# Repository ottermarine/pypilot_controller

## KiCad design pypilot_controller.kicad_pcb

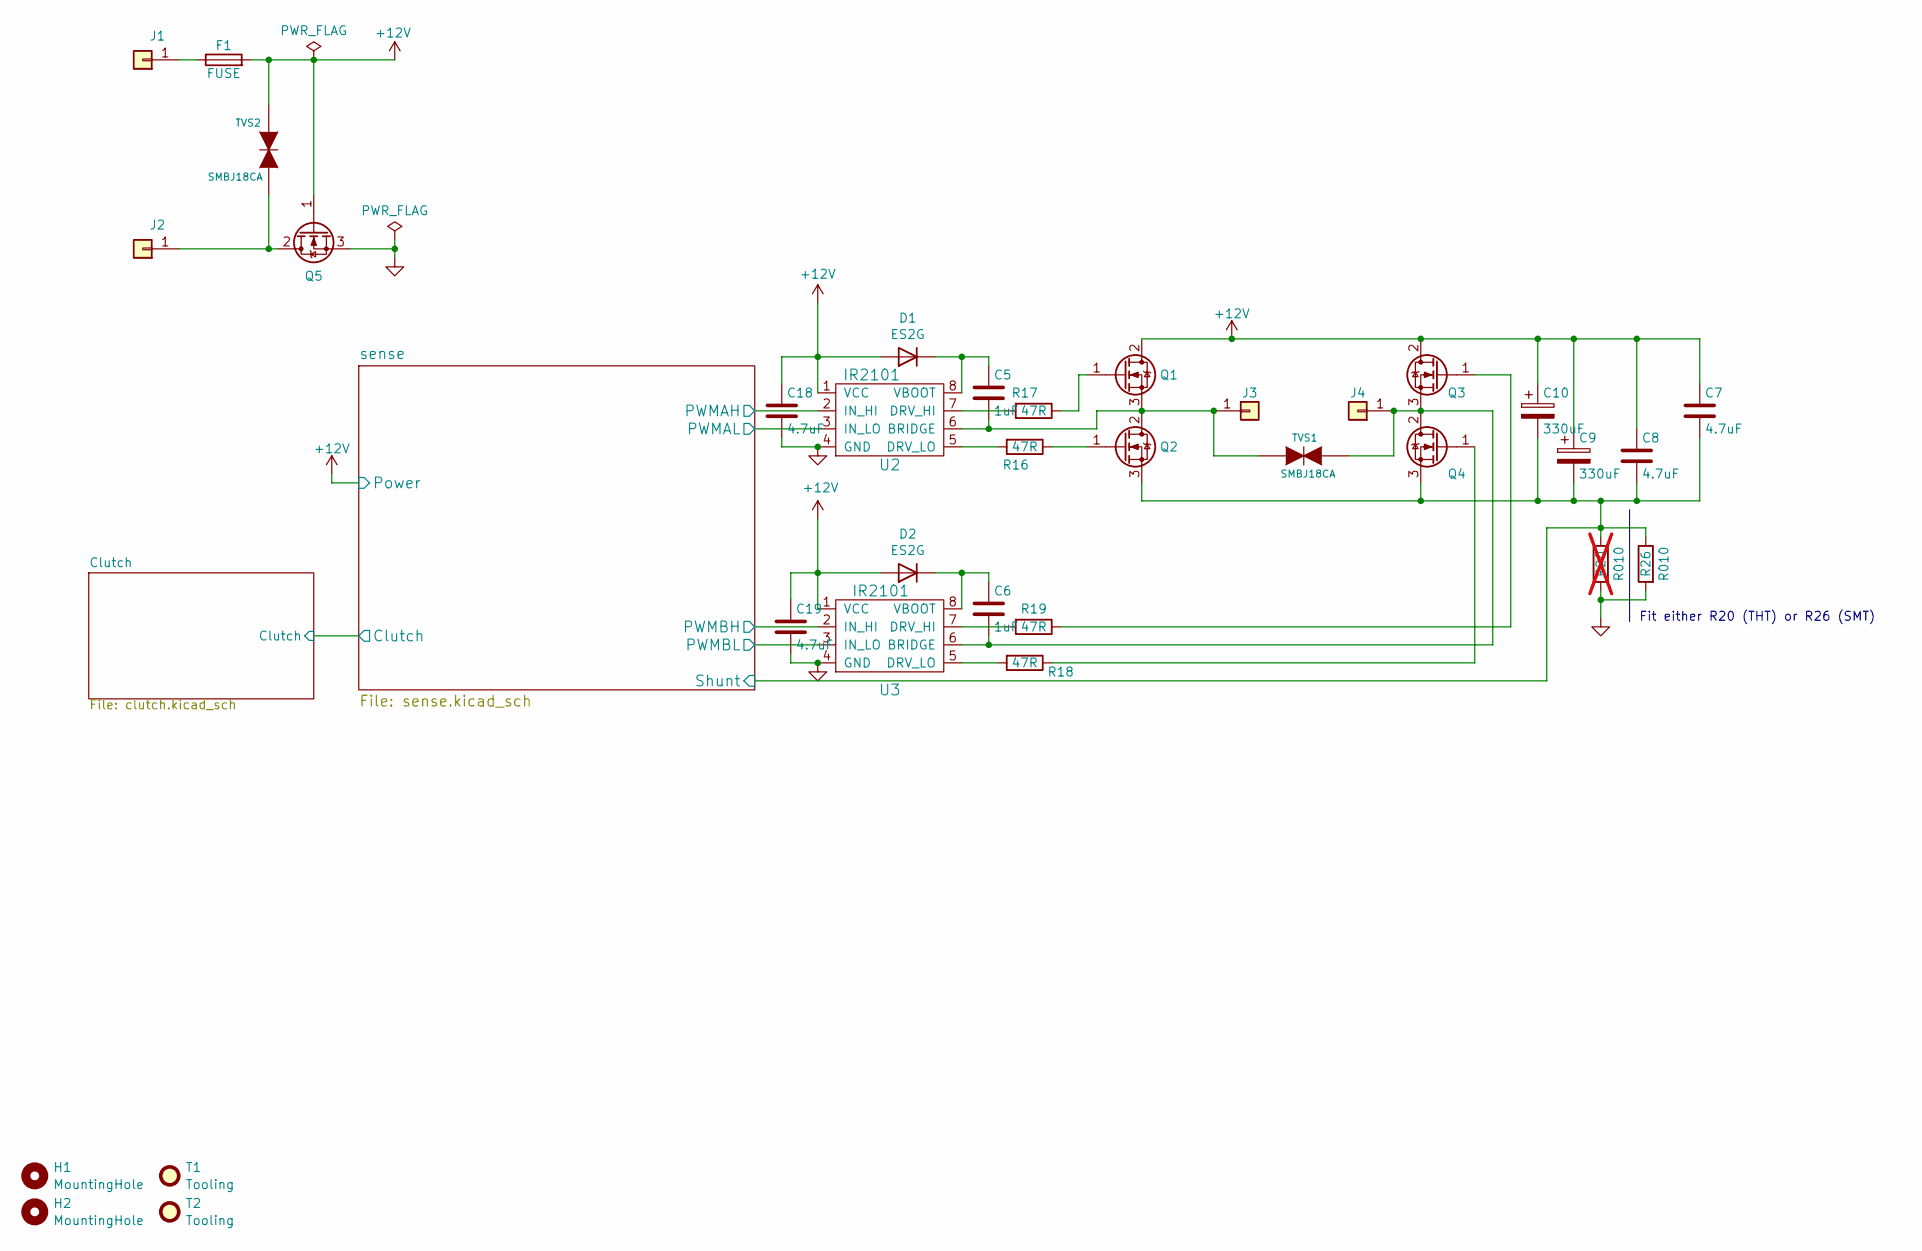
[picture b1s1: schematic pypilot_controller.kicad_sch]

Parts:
C5, C6: 1uF; C_0805_2012Metric; LCSC C28323
C7, C8, C18, C19: 4.7uF; C_1206_3216Metric; LCSC C29823
C9, C10: 330uF; CP_Radial_D10.0mm_P5.00mm; LCSC C357629
D1, D2: ES2G; D_SMA; LCSC C2848675
F1: FUSE; FUSE-TH_BX503-35; LCSC C2935871
H1, H2: MountingHole; MountingHole_2.5mm
J1: power+; CONN-TH_T44001; LCSC C481447
J2: power-; CONN-TH_T44001; LCSC C481447
J3: Motor A; CONN-TH_T44001; LCSC C481447
J4: Motor B; CONN-TH_T44001; LCSC C481447
Q1, Q2, Q3, Q4, Q5: IRFR7440; TO-252-2-reduced-paste; LCSC C97244
R16, R17, R18, R19: 47R; R_0805_2012Metric; LCSC C17714
R20: R010; R_Axial_DIN0207_L6.3mm_D2.5mm_P15.24mm_Horizontal; not fitted
R26: R010; R_2512_6332Metric; LCSC C105366
T1, T2: Tooling; JLC_Tooling_Hole
TVS1, TVS2: SMBJ18CA; D_SMB_TVS; LCSC C83327
U2, U3: IR2101; SOIC-8_3.9x4.9mm_P1.27mm; LCSC C2956

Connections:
+12V: C7.1, C8.1, C9.1, C10.1, C18.1, C19.1, D1.2 (A), D2.2 (A), F1.2, Q1.2 (D), Q3.2 (D), Q5.1 (G), TVS2.2 (K), U2.1 (VCC), U3.1 (VCC); also elsewhere on the board
/sense/PWMAH: U2.2 (IN_HI); also elsewhere on the board
/sense/PWMAL: U2.3 (IN_LO); also elsewhere on the board
/sense/PWMBH: U3.2 (IN_HI); also elsewhere on the board
/sense/PWMBL: U3.3 (IN_LO); also elsewhere on the board
/sense/Shunt: C7.2, C8.2, C9.2, C10.2, Q2.3 (S), Q4.3 (S), R20.1, R26.1; also elsewhere on the board
GND: C18.2, C19.2, Q5.3 (S), R20.2, R26.2, U2.4 (GND), U3.4 (GND); also elsewhere on the board
unnamed: C5.1, D1.1 (K), U2.8 (VBOOT)
unnamed: C6.1, D2.1 (K), U3.8 (VBOOT)
unnamed: F1.1, J1.1
unnamed: J2.1, Q5.2 (D), TVS2.1 (A)
unnamed: C5.2, J3.1, Q1.3 (S), Q2.2 (D), TVS1.2 (K), U2.6 (BRIDGE)
unnamed: C6.2, J4.1, Q3.3 (S), Q4.2 (D), TVS1.1 (A), U3.6 (BRIDGE)
unnamed: Q1.1 (G), R17.1
unnamed: Q2.1 (G), R16.1
unnamed: Q3.1 (G), R19.1
unnamed: Q4.1 (G), R18.1
unnamed: R17.2, U2.7 (DRV_HI)
unnamed: R16.2, U2.5 (DRV_LO)
unnamed: R19.2, U3.7 (DRV_HI)
unnamed: R18.2, U3.5 (DRV_LO)

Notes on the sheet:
Fit either R20 (THT) or R26 (SMT)

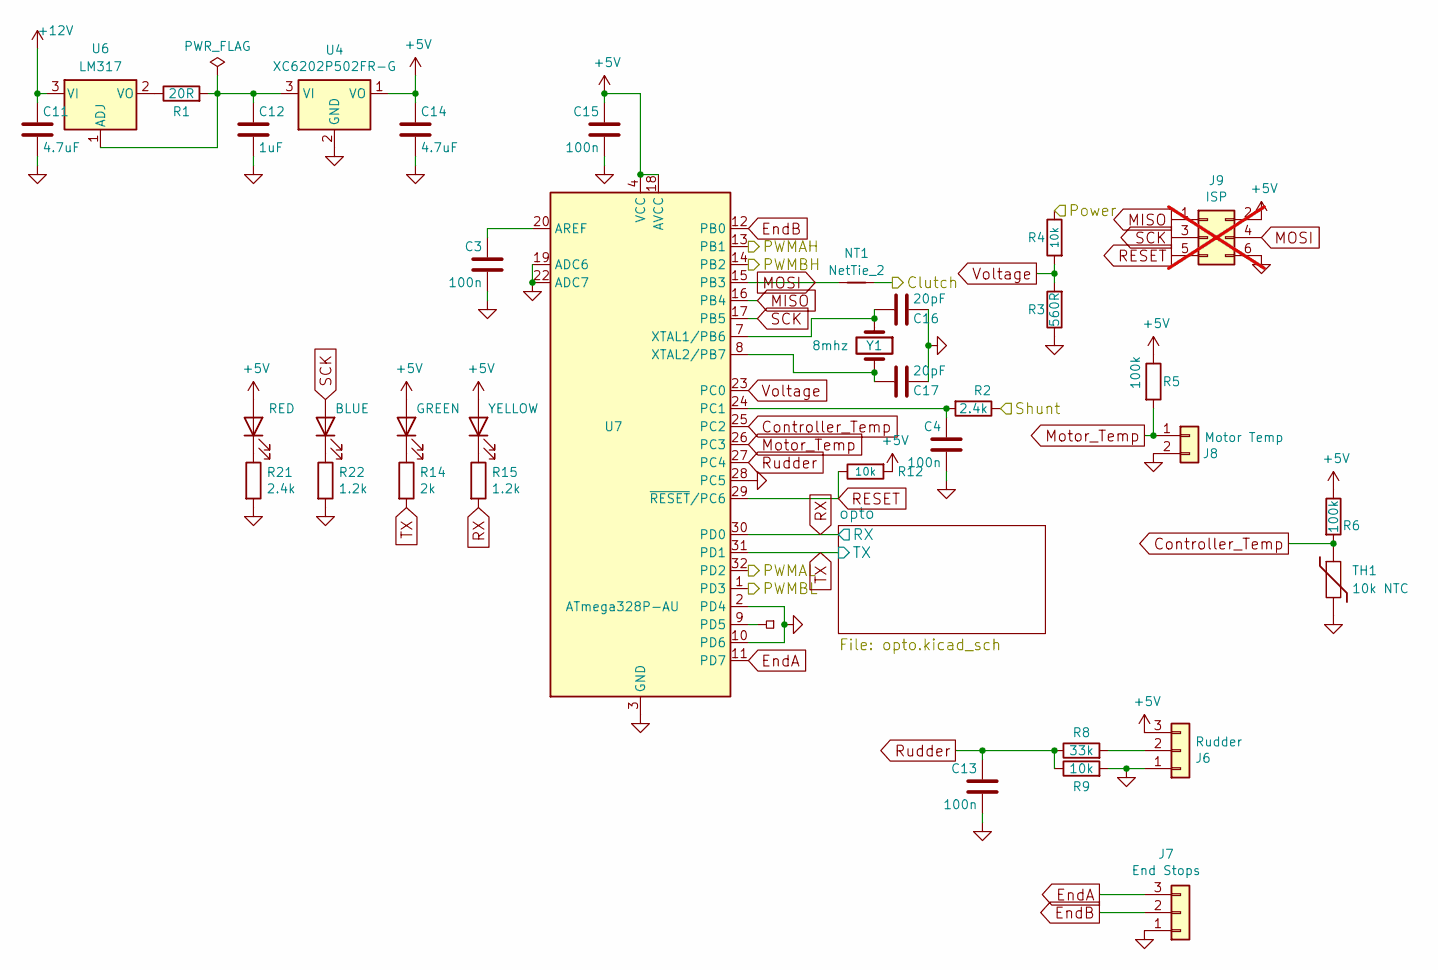
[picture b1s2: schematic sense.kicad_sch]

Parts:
C3, C4, C13, C15: 100n; C_0805_2012Metric; LCSC C49678
C11, C14: 4.7uF; C_1206_3216Metric; LCSC C29823
C12: 1uF; C_0805_2012Metric; LCSC C28323
C16, C17: 20pF; C_0805_2012Metric; LCSC C1798
J6: Rudder; PinHeader_1x03_P2.54mm_Vertical; LCSC C19190477
J7: End Stops; PinHeader_1x03_P2.54mm_Vertical; LCSC C19190477
J8: Motor Temp; PinHeader_1x02_P2.54mm_Vertical; LCSC C7494857
J9: ISP; PinHeader_2x03_P2.54mm_Vertical_SMD; LCSC C192301; not fitted
JP1: PCB_Pin_Breakout; TestPoint_Pad_1.0mm
LED1: RED; LED_0805_2012Metric; LCSC C84256
LED2: BLUE; LED_0603_1608Metric; LCSC C2290
LED3: GREEN; LED_0805_2012Metric; LCSC C2297
LED4: YELLOW; LED_0805_2012Metric; LCSC C2296
NT1: NetTie_2; NetTie-2_SMD_Pad0.5mm
R1: 20R; R_1206_3216Metric; LCSC C17955
R2, R21: 2.4k; R_0805_2012Metric; LCSC C17526
R3: 560R; R_0805_2012Metric; LCSC C28636
R4, R9, R12: 10k; R_0805_2012Metric; LCSC C17414
R5, R6: 100k; R_0805_2012Metric; LCSC C149504
R8: 33k; R_0805_2012Metric; LCSC C17633
R14: 2k; R_0805_2012Metric; LCSC C17604
R15, R22: 1.2k; R_0805_2012Metric; LCSC C17379
TH1: 10k NTC; R_0805_2012Metric; LCSC C72672
U4: XC6202P502FR-G; SOT-223-3_TabPin2; LCSC C725695
U6: LM317; TO-252-2-reduced-paste; LCSC C68136
U7: ATmega328P-AU; TQFP-32_7x7mm_P0.8mm; LCSC C14877
Y1: 8mhz; Crystal_SMD_5032-2Pin_5.0x3.2mm; LCSC C115962

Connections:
+5V: C14.1, C15.1, J6.3, J9.2, LED1.2 (A), LED3.2 (A), LED4.2 (A), R5.1, R6.1, R12.2, U4.1 (VO), U7.4 (VCC), U7.6 (VCC), U7.18 (AVCC); also elsewhere on the board
+12V: C11.1, R4.1, U6.3 (VI); also elsewhere on the board
/Clutch/Clutch: NT1.2; also elsewhere on the board
/sense/PWMAH: U7.13 (PB1); also elsewhere on the board
/sense/PWMAL: U7.32 (PD2); also elsewhere on the board
/sense/PWMBH: U7.14 (PB2); also elsewhere on the board
/sense/PWMBL: U7.1 (PD3); also elsewhere on the board
/sense/Shunt: R2.1; also elsewhere on the board
Controller_Temp: R6.2, TH1.1, U7.25 (PC2)
EndA: J7.3, U7.11 (PD7)
EndB: J7.2, U7.12 (PB0)
GND: C3.2, C4.2, C11.2, C12.2, C13.2, C14.2, C15.2, C16.1, C17.1, J6.1, J7.1, J8.2, J9.6, R3.1, R9.2, R21.2, R22.2, TH1.2, U4.2 (GND), U7.2 (PD4), U7.3 (GND), U7.5 (GND), U7.10 (PD6), U7.19 (ADC6), U7.21 (GND), U7.22 (ADC7), U7.28 (PC5); also elsewhere on the board
MISO: J9.1, U7.16 (PB4)
MOSI: J9.4, NT1.1, U7.15 (PB3)
Motor_Temp: J8.1, R5.2, U7.26 (PC3)
unnamed: J6.2, R8.2
unnamed: LED1.1 (K), R21.1
unnamed: LED2.1 (K), R22.1
unnamed: LED3.1 (K), R14.1
unnamed: LED4.1 (K), R15.1
unnamed: C12.1, R1.2, U4.3 (VI), U6.1 (ADJ)
unnamed: R1.1, U6.2 (VO)
unnamed: C3.1, U7.20 (AREF)
unnamed: C4.1, R2.2, U7.24 (PC1)
unnamed: JP1.1, U7.9 (PD5)
unnamed: C16.2, U7.7 (XTAL1/PB6), Y1.1
unnamed: C17.2, U7.8 (XTAL2/PB7), Y1.2
RESET: J9.5, R12.1, U7.29 (~RESET/PC6)
RX: R15.2, U7.30 (PD0); also elsewhere on the board
Rudder: C13.1, R8.1, R9.1, U7.27 (PC4)
SCK: J9.3, LED2.2 (A), U7.17 (PB5)
TX: R14.2, U7.31 (PD1); also elsewhere on the board
Voltage: R3.2, R4.2, U7.23 (PC0)

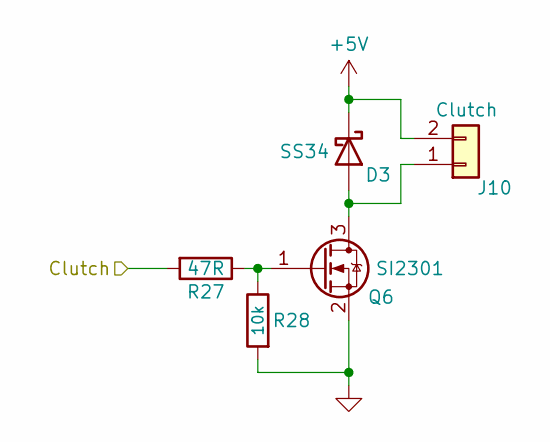
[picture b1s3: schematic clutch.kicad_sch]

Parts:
D3: SS34; D_SMA; LCSC C8678
J10: Clutch; PinHeader_1x02_P2.54mm_Vertical; LCSC C7494857
Q6: SI2301; SOT-23; LCSC C10487
R27: 47R; R_0805_2012Metric; LCSC C17714
R28: 10k; R_0805_2012Metric; LCSC C17414

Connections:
+5V: D3.1 (K), J10.2; also elsewhere on the board
/Clutch/Clutch: R27.2; also elsewhere on the board
GND: Q6.2 (S), R28.2; also elsewhere on the board
unnamed: D3.2 (A), J10.1, Q6.3 (D)
unnamed: Q6.1 (G), R27.1, R28.1

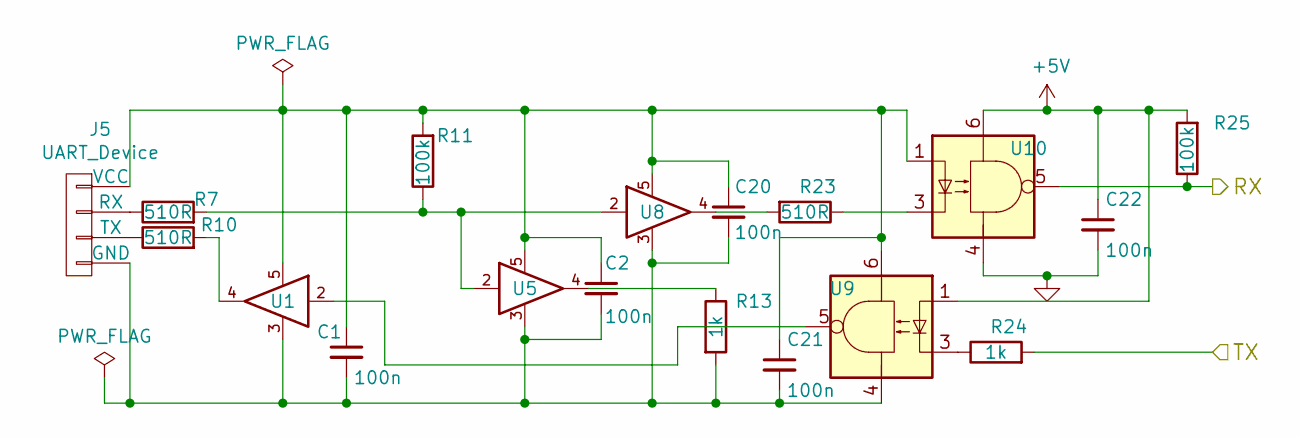
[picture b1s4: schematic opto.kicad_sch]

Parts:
C1, C2, C20, C21, C22: 100n; C_0805_2012Metric; LCSC C49678
J5: UART_Device; uart
R7, R10, R23: 510R; R_0805_2012Metric; LCSC C17734
R11, R25: 100k; R_0805_2012Metric; LCSC C149504
R13, R24: 1k; R_0805_2012Metric; LCSC C17513
U1, U5, U8: SN74LVC1G17DBVR; SOT-23-5; LCSC C7836
U9, U10: TLP2361(TPL,E(T; SO-5_4.4x3.6mm_P1.27mm; LCSC C107626

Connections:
+5V: C22.1, R25.2, U9.1, U10.6; also elsewhere on the board
GND: C22.2, U10.4; also elsewhere on the board
unnamed: C1.2, C2.2, C20.2, C21.2, J5.4 (GND), R13.2, U1.3, U5.3, U8.3, U9.4
unnamed: J5.2 (RX), R7.1
unnamed: J5.3 (TX), R10.1
unnamed: C1.1, C2.1, C20.1, C21.1, J5.1 (VCC), R11.2, U1.5, U5.5, U8.5, U9.6, U10.1
unnamed: R10.2, U1.4
unnamed: R7.2, R11.1, U5.2, U8.2
unnamed: R13.1, U5.4
unnamed: R23.1, U10.3
unnamed: R23.2, U8.4
unnamed: R24.1, U9.3
unnamed: U1.2, U9.5
RX: R25.1, U10.5; also elsewhere on the board
TX: R24.2; also elsewhere on the board

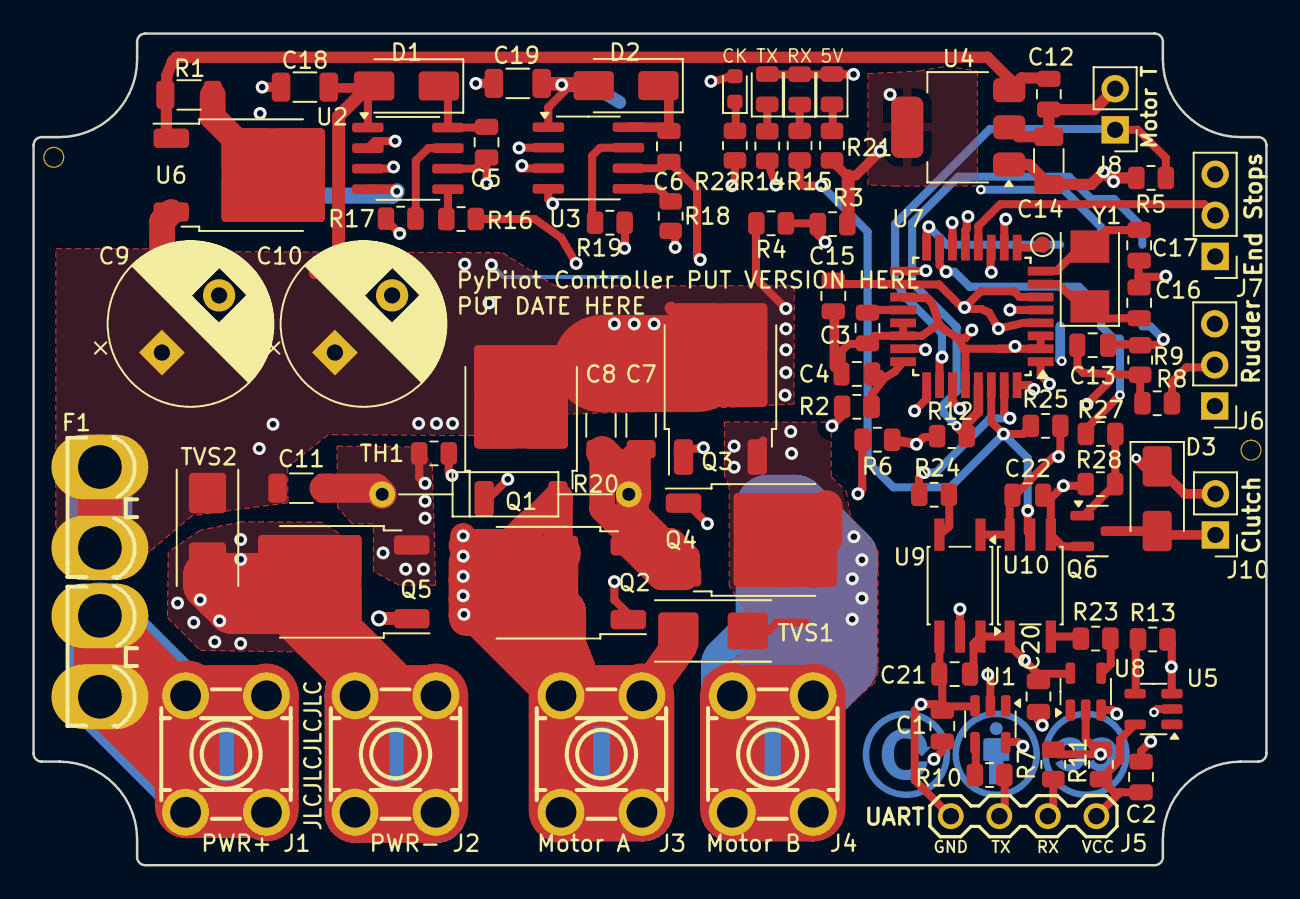
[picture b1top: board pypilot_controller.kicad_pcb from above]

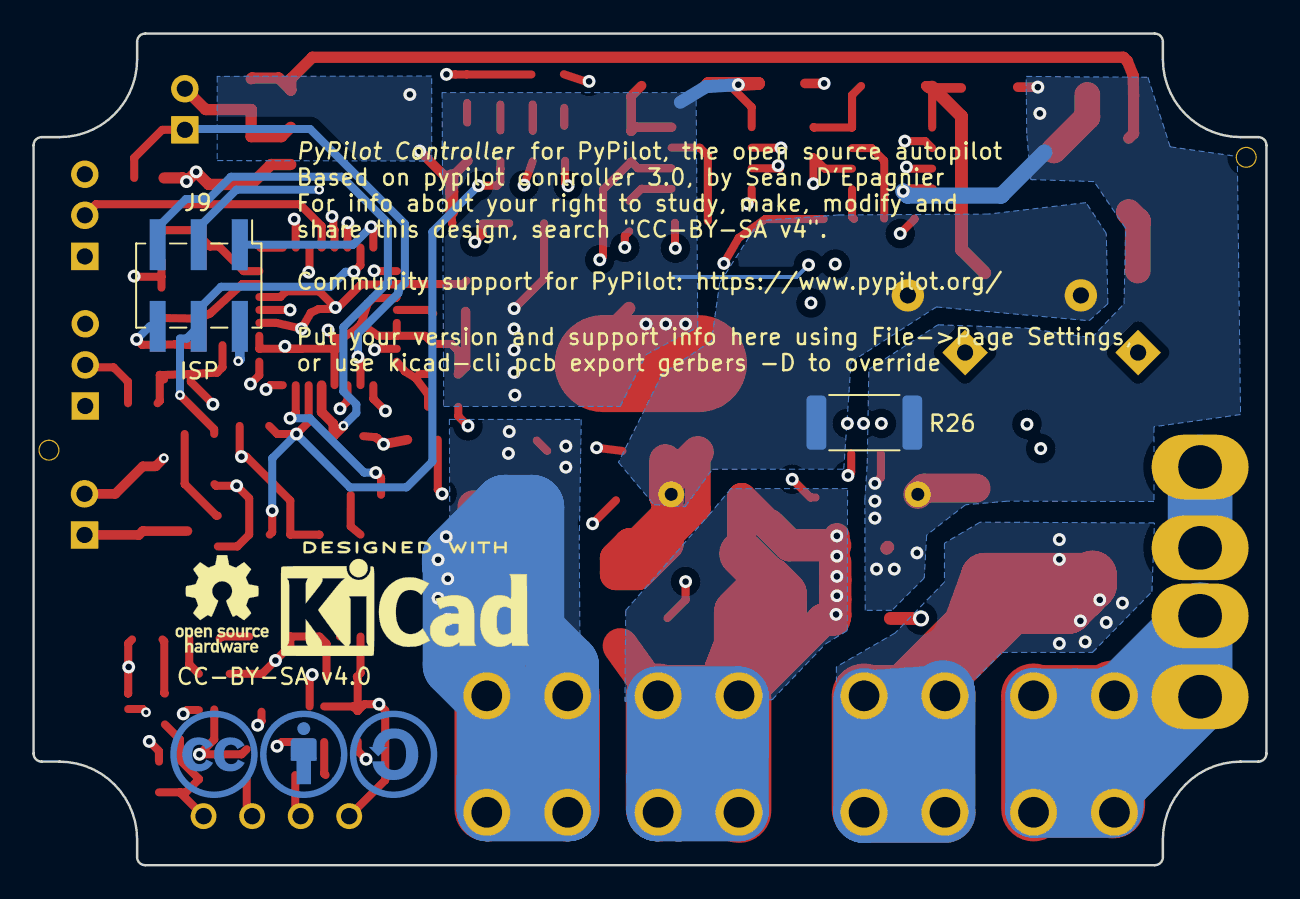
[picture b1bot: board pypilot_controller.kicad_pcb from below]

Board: 4 copper layers, 76.2 x 51.4 mm, 94 parts (3 on the bottom side), 60 nets.

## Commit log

2024-12-04 Files as received from Sean
2024-12-04 Ignore /old/ subdir
2024-12-04 Attempt to merge settings from .pro and .kicad_pro
2024-12-06 Provide missing freetronics_schematic and pypilot_components symbol libraries
    Recovered from pypilot_controller-rescue.kicad_sym, then converted to
    .kicad_sym format.
2024-12-06 Switch VCC to pypilot_controller symlib
    Because KiCad's VCC is an arrow, whereas the one that came with PyPilot
    is a circle. The VCC in pypilot_controller is the circle one.
2024-12-06 Switch to stock KiCad symbols that exist
2024-12-06 Switch to new style local symbol libs
2024-12-06 Remove old sym lib with rescued symbols
    All symbols in use have been carefully crosschecked to KiCad's stock
    symbols for differences.
2024-12-06 UART connector sym lib converted to new format
2024-12-06 Replaced .sch schematics with new-style .kicad_sch equivalents
2024-12-07 Tweak to format
    Make diffing easier
2024-12-07 Fix tlp2631 symbol recommended footprint from Package_SO:SO-6 to Package_SO:SO-5
2024-12-07 Switch footprints to stock KiCad versions, if the stock one is equivalent
2024-12-07 Move footprints into pypilot_controller_footprints, creating from PCB file if missing.
2024-12-07 Adjusted power pins on 74AHC1G125
2024-12-07 Use stock KiCad symbols instead of Freetronics ones.
2024-12-07 Rearrangement to keep KiCad happy
2024-12-07 Move the UART header symbol from the uart sym lib to pypilot_components sym lib
2024-12-07 Reconnect caps
    Stock symbols are smaller than the Freetronics ones were
2024-12-07 Patch in particular TVS model numbers
2024-12-08 First save of PCB with KiCad 8
    Gerbers are equivalent to originals
2024-12-08 Removed fab layers
    In this day and age of PnP machines, it's just noise.
2024-12-08 Replace 74AHC1G125 with 74LVC1G17
2024-12-08 Fix symbol for ISP header
2024-12-12 Add missing designators to schematic
2024-12-12 Add sheets to project file
2024-12-12 Fix missing wires around smaller cap symbols
2024-12-12 First pull of new footprints and net info from schematic to PCB
    It's obviously broken, many footprints aren't oriented or placed
    correctly
2024-12-14 Rename old nets from KiCad 5 PCB to match net names coming from schematic in KiCad 8
    KiCad has changed its algorithm for naming nets.
2024-12-14 Shifted MOSFET locations to match original board
    Centroid varies from original footprint
2024-12-15 Fixed MOSFET positions
    New footprint has a different centroid
2024-12-15 Updated UART footprint
    Esp the silk, and taking things off Eco1 layer
2024-12-15 Update footprint on PCB for R20, the shunt resistor
2024-12-15 Update footprint on PCB for R1, PSU ballast resistor
2024-12-15 Update footprints for 0805 resistors on PCB
2024-12-15 Remove silkscreen from screw terminal holes
2024-12-15 Remove silkscreen from footprint holes
2024-12-15 Update footprints on PCB for screw terminals, and fixed inconsistent alignment and track widths
2024-12-15 Fix drill size I messed up
2024-12-15 Updated footprint on PCB for F1
2024-12-15 Modified silkscreen of footprint to not be so wide
2024-12-15 Update footprint on PCB for TVS diodes
2024-12-15 Update footprints on PCB for everything with a TO-252-2 footprint
2024-12-15 Updated footprint on PCB for AMS1117
2024-12-15 Update footprints on PCB for SOIC-8 gate drivers
2024-12-15 Update footprints on PCB for SO-5 package optos.
2024-12-15 Update footprint on PCB for TQFP-32 ATmega328P
2024-12-15 Update footprints on PCB for 0805 LEDs
2024-12-15 Update footprints on PCB for 0603 LED
2024-12-15 Update footprints on PCB for gate driver charge pump SMA package diodes
    Expanded courtyard reqiured moving components a little
2024-12-15 Updated symbol for ISP header
    Numbering was still set to old order
2024-12-15 Updated footprint on PCB for ISP header
2024-12-15 Add ES2G diode and XC6202P502FR-G 5V 200mA LDO regulator to symbols
2024-12-15 Switch the charge pump diode symbol that's actually being used
2024-12-15 Fixed pin number problem
2024-12-15 Switch from using AMS1117-5.0 to XC6202P502FR-G 5V 200mA LDO regulator
    This is what's in the CSV file as the regulator that's being used
2024-12-15 Oops, should hide datasheet and footprint fields in TVS symbol
2024-12-15 Update every symbol in the schematic
2024-12-15 Add a hidden pin 1, and move power pins so wires can be connected in schematic editor
2024-12-15 Rework the opto circuit with smaller caps to reduce clutter.
2024-12-15 Pull from schematic, and update charge pump diodes, regulators and SOT-23-5 translators
2024-12-15 Update footprints on PCB for headers
2024-12-15 Fix a courtyard clearance problem
2024-12-16 Update footprints on PCB for electrolytics
2024-12-16 Update footprints on PCB for 1206 capacitors
2024-12-16 Update footprints on PCB for 0805 caps
2024-12-16 Update all symbols
    That it produced so little change confirms very little divergence from
    stock and custom symbols. Yippee!
2024-12-16 Changes KiCad keeps wanting to make to the project file
    Plus some from the original dump
2024-12-16 eeschema wants this line gone. Don't know why
2024-12-16 Added a stack-up, plus some gerber settings
2024-12-16 Added symbols for mounting and cable tie holes, to avoid warning on import from schematic
2024-12-16 Updated fuse footprint to have LCSC numbers
2024-12-16 Refill zones
    And make a small tweak to add another thermal relief to ground zone
2024-12-16 Tweaked licence doc, as per the CERN OHL howto
2024-12-16 Added text to silkscreen on front and back with authorship, licence and websites
2024-12-16 Switching to markdown format
2024-12-16 We no longer need this file
2024-12-17 Change list as required by CERN OHL P v2
2024-12-17 Moved some vias and silkscreen to make PyPilot Controller easier to read
2024-12-17 Eeschema wants to move mounting holes in file
2024-12-17 Moved some wires to be clearer
2024-12-17 New part numbers from schematic import
2024-12-17 Ignore generated files in the outputs/ dir
2024-12-17 Bump up size of version number in silkscreen
2024-12-18 Remove whitespace from LCSC field entries
2024-12-18 Use standard format for resistor values
2024-12-18 Tweak to display of components in bulk field editor
2024-12-18 Added version numbers to make variants easier to make
2024-12-18 Took my info out. This makes it easier for others to produce their own versions
2024-12-19 Updating U9/U10 opto symbols pulled symbol into .kicad_sch file
2024-12-19 Move hidden pin 1 to align to grid (removes ERC warning)
2024-12-19 Import fixes to resistor values and LCSC part numbers from schematic
2024-12-19 Move ISP header to the back of the board
2024-12-22 pcbnew wants to move posn of ISP header in file
2024-12-22 Add a surface mount shunt resistor to the back of the board
2024-12-22 Change license to CC-BY-SA v4.0
2024-12-22 Reverted version number/date, because it can be scripted
2024-12-22 Added KiCad logo and CC license icons to back of PCB
2024-12-22 C17 had LCSC part number for 12pF cap, but schematic says 18pF. Fixed.
2024-12-22 Lock kicad/OSHW/CC graphics so they don't disappear on import from schematic
2024-12-22 Update motor terminals to match silkscreen
2024-12-22 Pull from schematic
2024-12-22 Replaced VCC symbol/net with +12V (otherwise there's an ERC warning)
2024-12-22 eeschema wants this cached copy of the tlp2361 gone
2024-12-23 Remove 74AHC1G125, as we now only use the 74LVC1G17
2024-12-23 Rename NCP5106B to IR2102
2024-12-23 Turned off thermal relief for zone fills around the screw terminal
    (Fixes a problem where there was a gap in the copper near Motor B)
2024-12-23 Break out PD5, pin 9 of ATmega328
2024-12-23 Added tooling holes for JLC's assembly service
2024-12-23 Added JLCJLCJLCJLC to silkscreen so JLC know where to put their production code
2024-12-24 Unlock back of board graphics, but mark them as not in schematic to prevent removal
2024-12-24 Break out clutch pin to header
2024-12-24 A no-op footprint refresh for the TO-252 parts
    A nop
2024-12-24 Remove CERN OHL howto (this inadvertently crept in, the license is CC-BY-SA v4.0)
2024-12-24 Refresh of TO-252-2 footprints in prep for reduced paste version
2024-12-24 Change TO-252 footprint to use less solder paste
2024-12-24 Cleaned up designators - where possible, they are all right way up
2024-12-24 Added license tag and moved eye candy on reverse side around
2024-12-24 Moved posn of RED on LED1 to align with others
2024-12-24 Added reduced paste TO-252-2 footprint
2024-12-24 Fixed almost all ERC errors and warnings (now 0 errors, 3 warnings)
2024-12-24 Fixed up some net breakage caused by the on-copper graphics on the back
2024-12-24 Removed as many DRC errors and warnings as I could
2024-12-24 Track cleanups, mostly from Tools -> Cleanup Tracks & Vias
2024-12-24 Cleaned LCSC part numbers out of datasheet field (and renamed 0.1u to 100n)
2024-12-28 Replace crystal caps with a JLC PCBA basic part (20pF instead of 18pF)
2024-12-28 Show motor temp on J8, the motor temp connector
2024-12-28 Update TVS diodes to be cheapest of all the options Sean mentioned
2024-12-28 Import to pcb after refining component choice
2024-12-28 Updated screw terminals from C238164 to C481447, much cheaper
2024-12-28 Update 3d model and footprint for fuse holder
2024-12-28 Move TVS
2024-12-28 Fix zone around thermistor
2024-12-28 Fixed posn of MOSFET designators
2024-12-28 Put clutch components onto separate sheet
2024-12-28 Add MOSFET to switch a relay on the clutch output
2024-12-28 Tweaks to hand-load components for current availability
2025-01-04 Moved components away from isolation barrier
2025-01-22 Added a missing track in the opto section (rx pullup resistor)
2025-01-22 Changes from saving with KiCad 8.0.8
2025-01-22 Pull of component fields from schematic (mostly LCSC numbers)
2025-01-22 Ignore generated SVG files, and anything in extra/ subdir
2025-01-22 Modify board outline to fit Daho 83X58X34 enclosure. Remove mounting holes and move components.
2025-01-22 Mark ISP connector as DNP, so it doesn't appear in STEP export
2025-01-22 Set file name for STEP exports
2025-01-22 Change cable clamp holes to NPTH slots
2025-01-22 Added results of fit test to components received from LCSC
2025-01-22 Specify MOSFET
2025-01-22 Import fit test results from schematic
2025-01-22 Stretch electrocap models to 20mm tall
2025-01-22 Fatten slots for cable tie
2025-01-22 More fit test results
2025-01-22 Turn off thermal reliefs for J1-J4, to increase current capacity

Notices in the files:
pypilot_controller.kicad_pcb:
For info about your right to study, make, modify and
share this design, search \"CC-BY-SA v4\".
